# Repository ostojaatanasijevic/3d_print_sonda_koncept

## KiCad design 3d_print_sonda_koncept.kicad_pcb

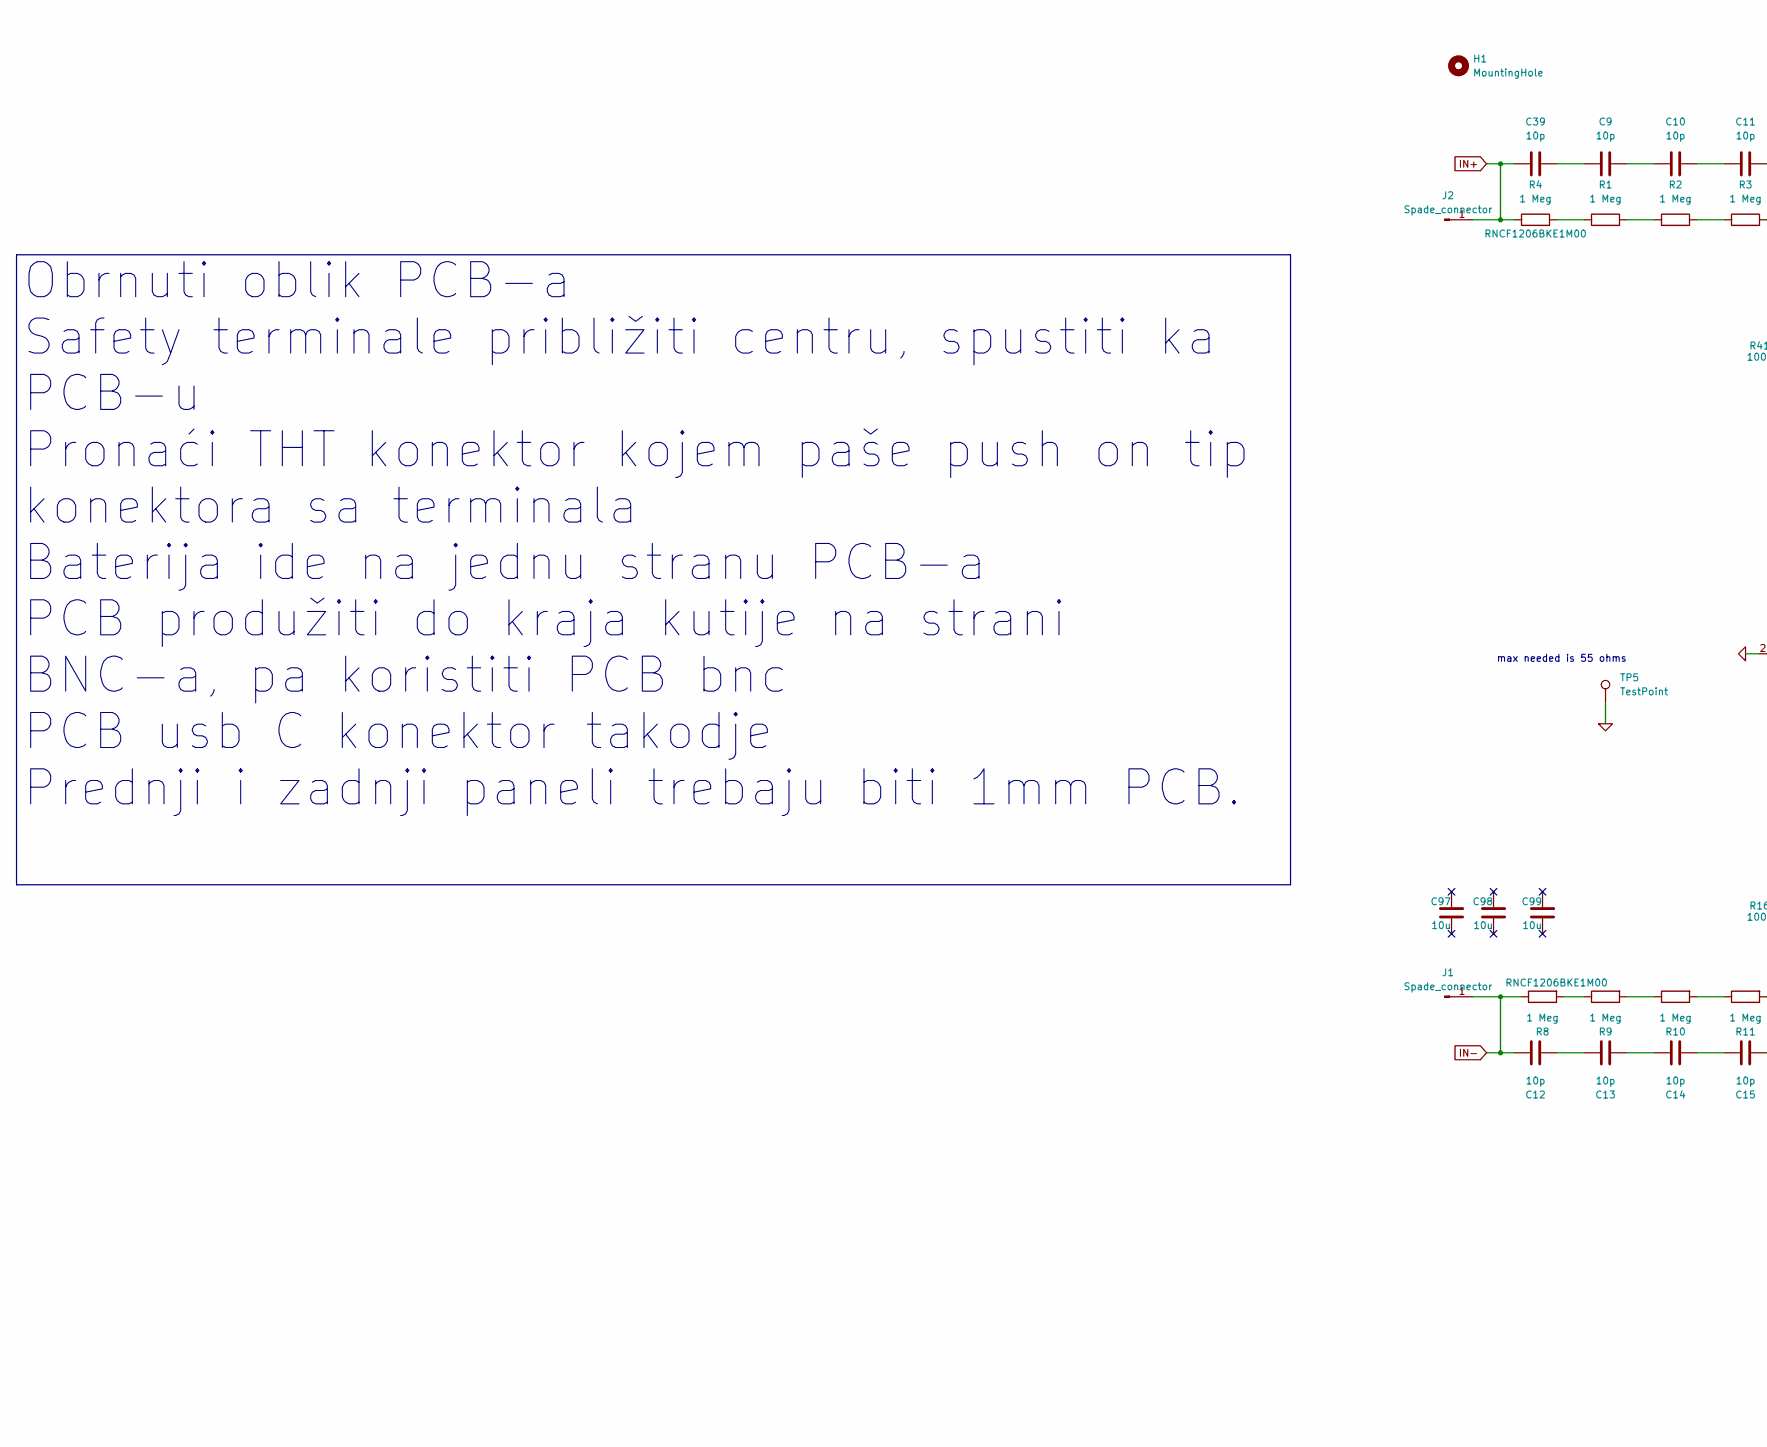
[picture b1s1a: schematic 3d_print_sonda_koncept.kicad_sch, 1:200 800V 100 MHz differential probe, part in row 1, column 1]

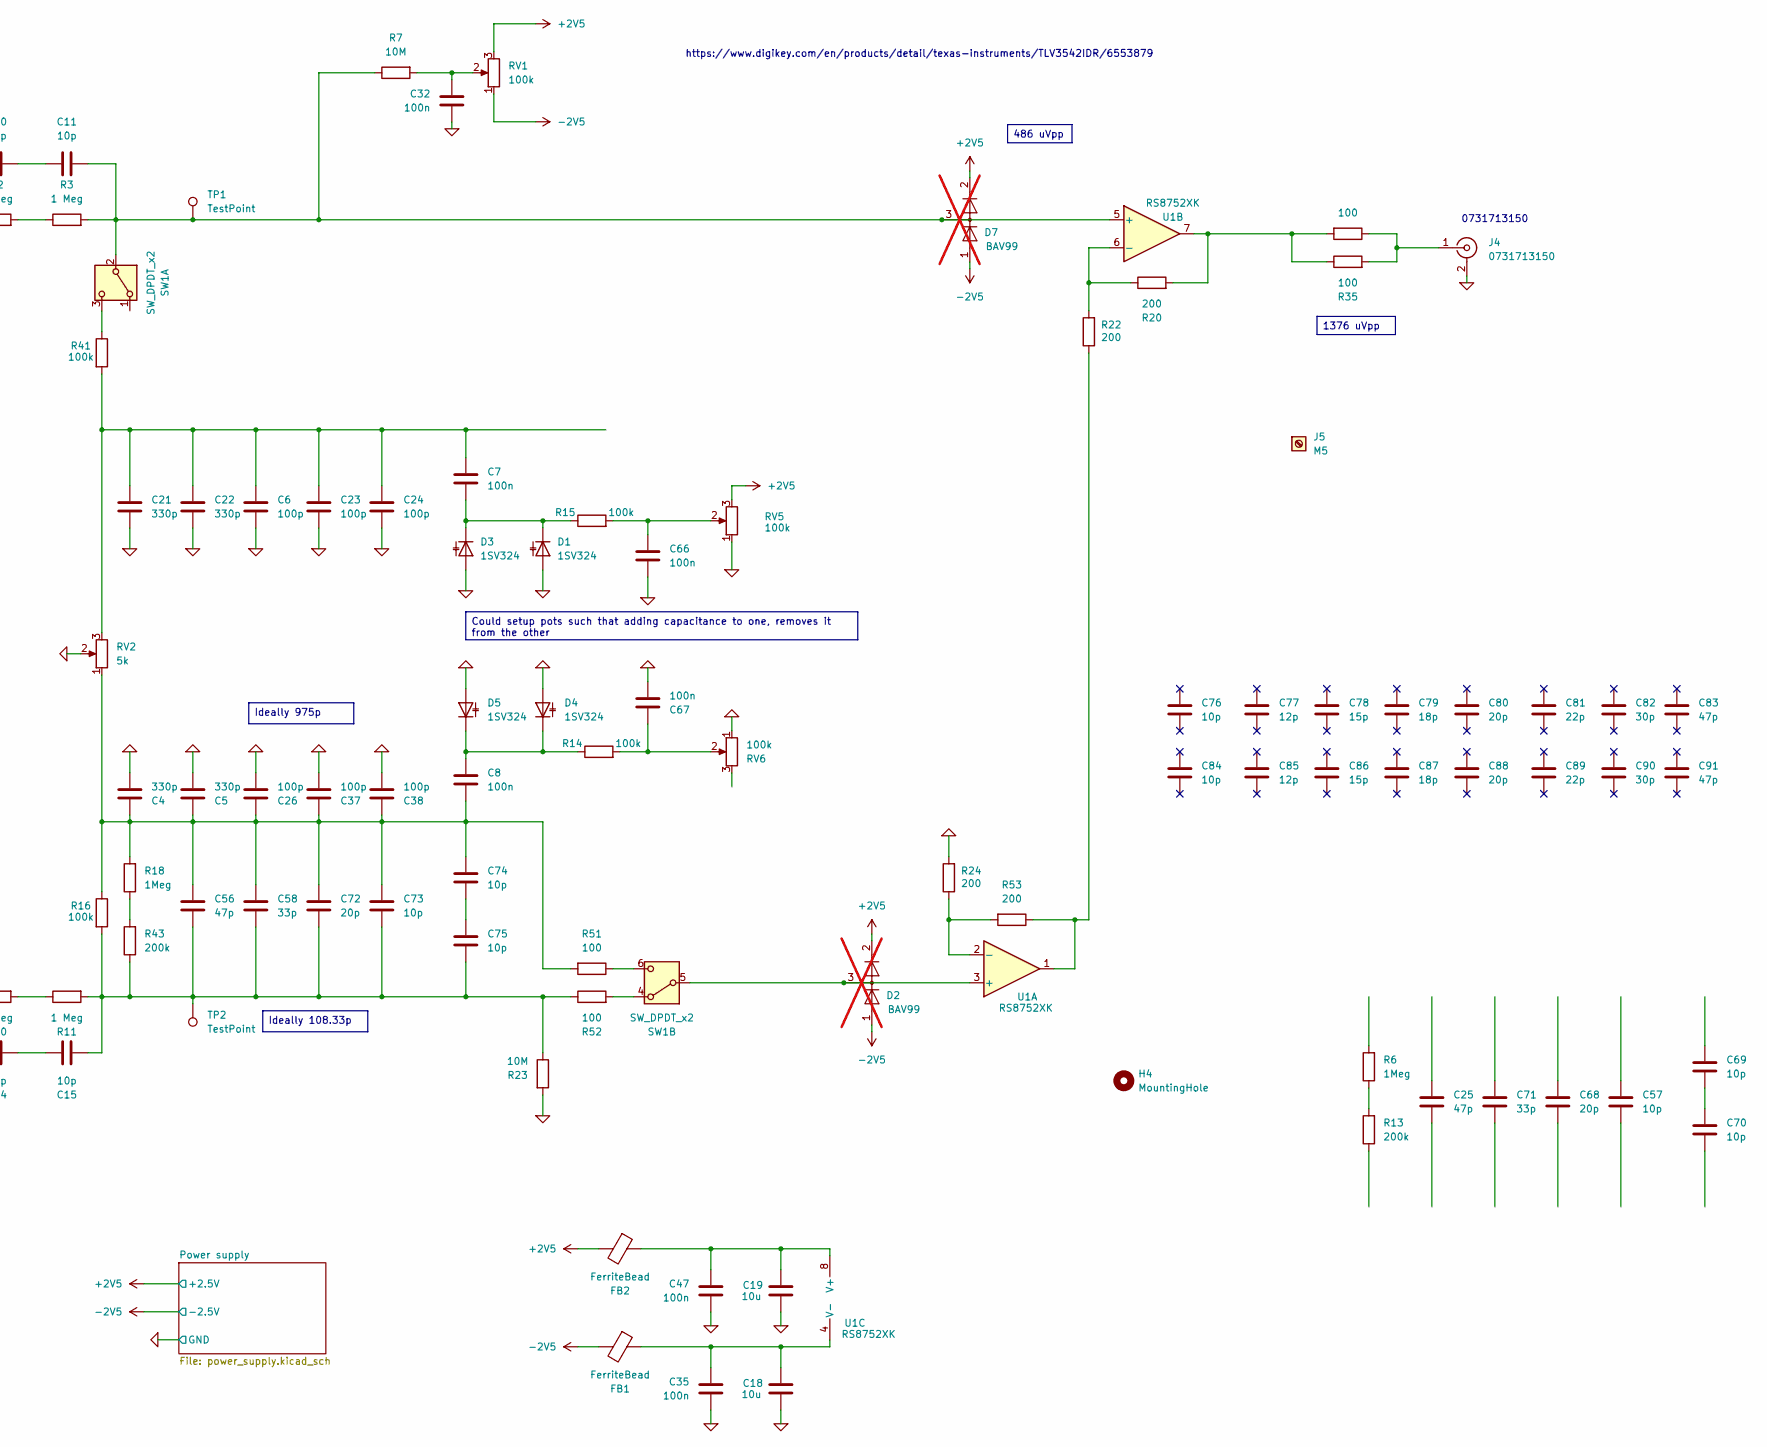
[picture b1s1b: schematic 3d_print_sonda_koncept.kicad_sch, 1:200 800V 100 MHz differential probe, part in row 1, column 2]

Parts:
C4, C5, C21, C22: 330p; R_0603_1608Metric_Pad0.98x0.95mm_HandSolder; LCSC C1664
C6, C23, C24, C26, C37, C38: 100p; R_0603_1608Metric_Pad0.98x0.95mm_HandSolder; LCSC C14858
C7, C8, C32, C35, C47, C66, C67: 100n; C_0603_1608Metric_Pad1.08x0.95mm_HandSolder; LCSC C14663
C9, C10, C11, C12, C13, C14, C15, C39: 10p; R_1206_3216Metric_Pad1.30x1.75mm_HandSolder
C18, C19: 10u; C_0603_1608Metric_Pad1.08x0.95mm_HandSolder; LCSC C96446
C25, C56, C83, C91: 47p; R_0603_1608Metric_Pad0.98x0.95mm_HandSolder; LCSC C1648
C57, C69, C70, C73, C74, C75, C76, C84: 10p; R_0603_1608Metric_Pad0.98x0.95mm_HandSolder; LCSC C1634
C58, C71: 33p; R_0603_1608Metric_Pad0.98x0.95mm_HandSolder; LCSC C1663
C68, C72, C80, C88: 20p; R_0603_1608Metric_Pad0.98x0.95mm_HandSolder; LCSC C1648
C77, C85: 12p; R_0603_1608Metric_Pad0.98x0.95mm_HandSolder; LCSC C38523
C78, C86: 15p; R_0603_1608Metric_Pad0.98x0.95mm_HandSolder; LCSC C1644
C79, C87: 18p; R_0603_1608Metric_Pad0.98x0.95mm_HandSolder; LCSC C1644
C81, C89: 22p; R_0603_1608Metric_Pad0.98x0.95mm_HandSolder; LCSC C1653
C82, C90: 30p; R_0603_1608Metric_Pad0.98x0.95mm_HandSolder; LCSC C1658
C97, C98, C99: 10u; R_0805_2012Metric_Pad1.20x1.40mm_HandSolder; Voltage 25V; LCSC C15850
D1, D3, D4, D5: 1SV324; D_SOD-323_HandSoldering
D2, D7: BAV99; SOT-23; LCSC C2500; not fitted
FB1, FB2: FerriteBead; L_0603_1608Metric_Pad1.05x0.95mm_HandSolder
H1, H4: MountingHole; M3_with_screw
J1, J2: Spade_connector; spade_connector_mid_PCB
J4: 0731713150; 5414373-1
J5: M5; M5_floating
R1, R2, R3, R9, R10, R11: 1 Meg; R_1206_3216Metric_Pad1.30x1.75mm_HandSolder
R4, R8: 1 Meg; R_1206_3216Metric_Pad1.30x1.75mm_HandSolder; Partnumber RNCF1206BKE1M00
R6, R18: 1Meg; R_0603_1608Metric_Pad0.98x0.95mm_HandSolder; LCSC C22935
R7, R23: 10M; R_0603_1608Metric_Pad0.98x0.95mm_HandSolder; LCSC C7250
R13, R43: 200k; R_0603_1608Metric_Pad0.98x0.95mm_HandSolder; LCSC C25811
R14, R15, R16, R41: 100k; R_0603_1608Metric_Pad0.98x0.95mm_HandSolder; LCSC C25803
R17, R35, R51, R52: 100; R_0603_1608Metric_Pad0.98x0.95mm_HandSolder; LCSC C22775
R20, R22, R24, R53: 200; R_0603_1608Metric_Pad0.98x0.95mm_HandSolder
RV1, RV5, RV6: 100k; Potentiometer_Bourns_3296W_Vertical
RV2: 5k; Potentiometer_Bourns_3296W_Vertical
SW1: SW_DPDT_x2; DPDT_bigger
TP1, TP2, TP5: TestPoint; TestPoint_Pad_D2.0mm
U1: RS8752XK; SOIC-8_3.9x4.9mm_P1.27mm; LCSC RS8752XK

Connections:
0: C4.2, C5.2, C6.1, C18.2, C19.2, C21.2, C22.2, C23.1, C24.1, C26.1, C32.1, C35.1, C37.1, C38.1, C47.1, C66.1, C67.1, D1.2 (A), D3.2 (A), D4.2 (A), D5.2 (A), J4.2 (Ext), R23.2, R24.2, RV2.2, RV5.1, RV6.1, TP5.1; also elsewhere on the board
+2V5: D2.2 (A), D7.2 (A), FB2.2, RV1.3, RV5.3; also elsewhere on the board
-2V5: D2.1 (K), D7.1 (K), FB1.2, RV1.1; also elsewhere on the board
IN+: C39.2, J2.1, R4.1
IN-: C12.2, J1.1, R8.1
unnamed: C10.1, C11.2
unnamed: C9.1, C10.2
unnamed: C12.1, C13.2
unnamed: C13.1, C14.2
unnamed: C14.1, C15.2
unnamed: C15.1, C56.1, C58.1, C72.1, C73.1, C75.1, R11.2, R16.2, R23.1, R43.1, R52.1, TP2.1
unnamed: C6.2, C7.2, C21.1, C22.1, C23.2, C24.2, R41.2, RV2.3
unnamed: C4.1, C5.1, C8.1, C26.2, C37.2, C38.2, C56.2, C58.2, C72.2, C73.2, C74.2, R16.1, R18.2, R51.2, RV2.1
unnamed: C32.2, R7.2, RV1.2
unnamed: C9.2, C39.1
unnamed: C66.2, R15.2, RV5.2
unnamed: C67.2, R14.2, RV6.2
unnamed: C69.1, C70.2
unnamed: C74.1, C75.2
unnamed: C7.1, D1.1 (K), D3.1 (K), R15.1
unnamed: C8.2, D4.1 (K), D5.1 (K), R14.1
unnamed: J4.1 (In), R17.1, R35.2
unnamed: R1.1, R4.2
unnamed: R1.2, R2.1
unnamed: R2.2, R3.1
unnamed: R8.2, R9.1
unnamed: R9.2, R10.1
unnamed: R10.2, R11.1
unnamed: R6.1, R13.2
unnamed: R17.2, R20.2, R35.1, U1.7
unnamed: R18.1, R43.2
unnamed: R22.1, R53.1, U1.1
unnamed: C11.1, D7.3 (K), R3.2, R7.1, SW1.2 (B), TP1.1, U1.5 (+)
unnamed: R41.1, SW1.3 (C)
unnamed: R52.2, SW1.4 (A)
unnamed: D2.3 (K), SW1.5 (B), U1.3 (+)
unnamed: R51.1, SW1.6 (C)
unnamed: R24.1, R53.2, U1.2 (-)
unnamed: R20.1, R22.2, U1.6 (-)
unnamed: C19.1, C47.2, FB2.1, U1.8 (V+)
unnamed: C18.1, C35.2, FB1.1, U1.4 (V-)

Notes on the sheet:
https://www.digikey.com/en/products/detail/texas-instruments/TLV3542IDR/6553879
max needed is 55 ohms
0731713150
1376 uVpp
Ideally 108.33p
Ideally 975p
486 uVpp
Could setup pots such that adding capacitance to one, removes it from the other
Obrnuti oblik PCB-a Safety terminale približiti centru, spustiti ka PCB-u Pronaći THT konektor kojem paše push on tip konektora sa terminala Baterija ide na jednu stranu PCB-a PCB produžiti do kraja kutije na strani BNC-a, pa koristiti PCB bnc PCB usb C konektor takodje Prednji i zadnji paneli treb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

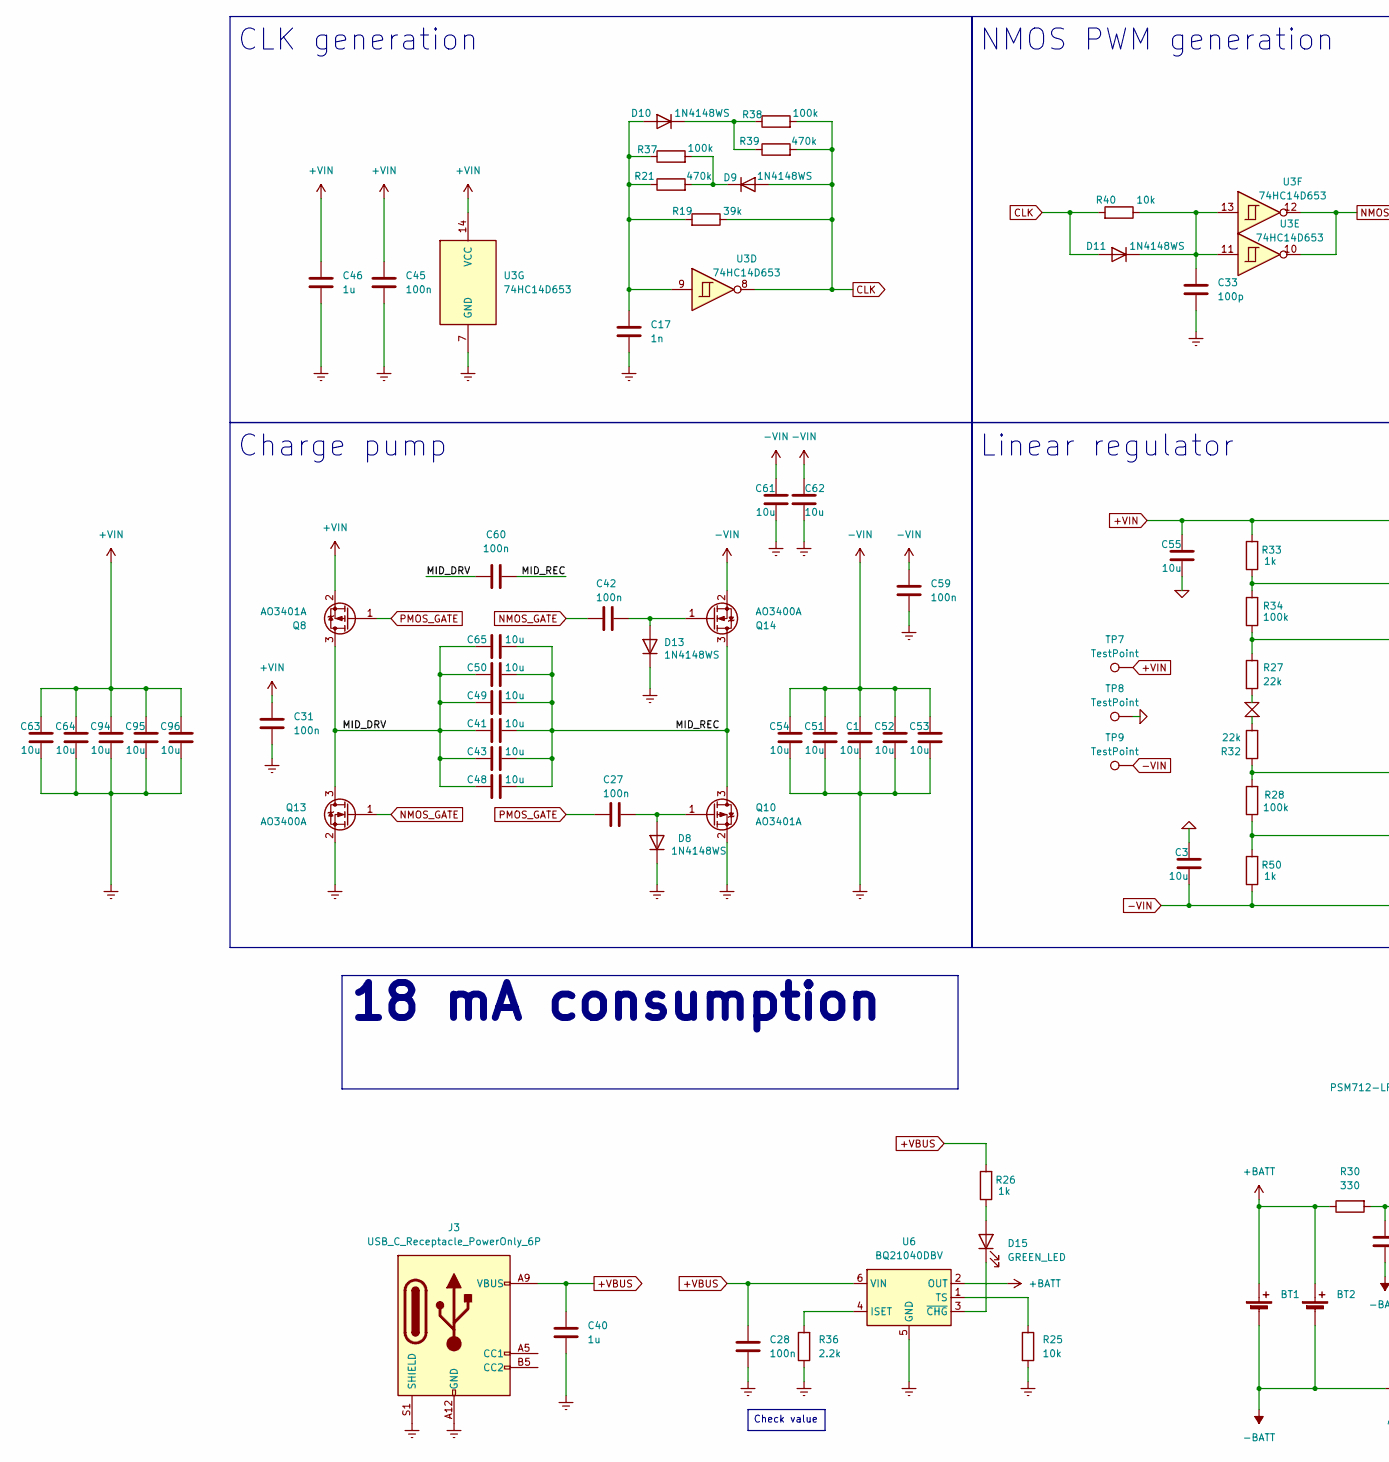
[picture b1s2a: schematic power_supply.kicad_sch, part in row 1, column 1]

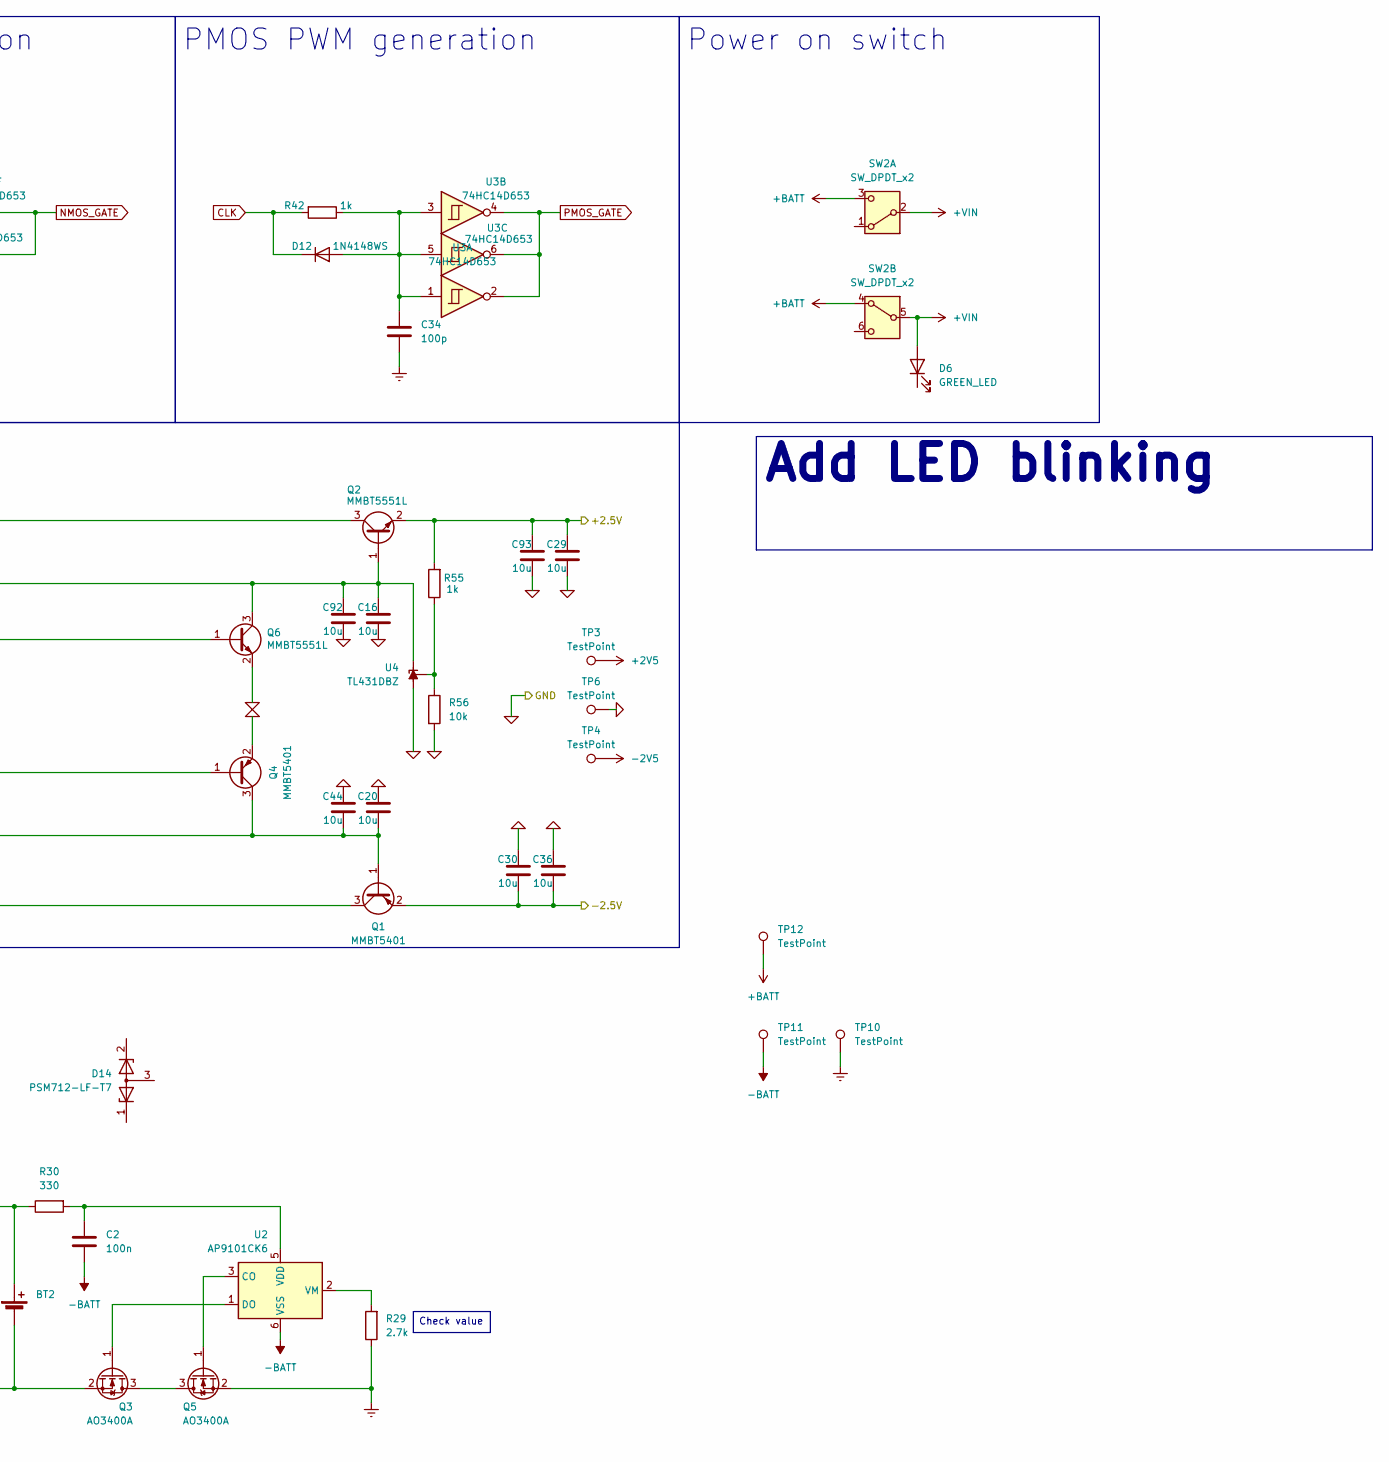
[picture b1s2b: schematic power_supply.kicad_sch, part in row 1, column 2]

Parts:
BT1, BT2: Battery_Cell; battery_holder
C1, C3, C16, C20, C29, C30, C36, C41, C43, C44, C48, C49, C50, C51, C52, C53, C54, C55, C61, C62, C63, C64, C65, C92, C93, C94, C95, C96: 10u; R_0805_2012Metric_Pad1.20x1.40mm_HandSolder; Voltage 25V; LCSC C15850
C2, C27, C28, C31, C42, C45, C59, C60: 100n; C_0603_1608Metric_Pad1.08x0.95mm_HandSolder; LCSC C14663
C17: 1n; C_0603_1608Metric_Pad1.08x0.95mm_HandSolder; LCSC C1588
C33, C34: 100p; C_0603_1608Metric_Pad1.08x0.95mm_HandSolder; LCSC C14858
C40, C46: 1u; C_0603_1608Metric_Pad1.08x0.95mm_HandSolder; LCSC C15849
D6, D15: GREEN_LED; LED_0805_2012Metric_Pad1.15x1.40mm_HandSolder; LCSC C2297
D8, D9, D10, D11, D12, D13: 1N4148WS; D_SOD-323; LCSC C2128
D14: PSM712-LF-T7; SOT-23_Handsoldering; LCSC C32677
J3: USB_C_Receptacle_PowerOnly_6P; USB_C_Receptacle_GCT_USB4125-xx-x-0190_6P_TopMnt_Horizontal
Q1, Q4: MMBT5401; SOT-23; LCSC C8326
Q2, Q6: MMBT5551L; SOT-23; LCSC C2145
Q3, Q5, Q13, Q14: AO3400A; SOT-23; LCSC C20917
Q8, Q10: AO3401A; SOT-23; LCSC C15127
R19: 39k; R_0603_1608Metric_Pad0.98x0.95mm_HandSolder; LCSC C23153
R21, R39: 470k; R_0603_1608Metric_Pad0.98x0.95mm_HandSolder; LCSC C23178
R25, R40, R56: 10k; R_0603_1608Metric_Pad0.98x0.95mm_HandSolder; LCSC C25804
R26, R33, R42, R50, R55: 1k; R_0603_1608Metric_Pad0.98x0.95mm_HandSolder; LCSC C21190
R27, R32: 22k; R_0603_1608Metric_Pad0.98x0.95mm_HandSolder; LCSC C31850
R28, R34, R37, R38: 100k; R_0603_1608Metric_Pad0.98x0.95mm_HandSolder; LCSC C25803
R29: 2.7k; R_0603_1608Metric_Pad0.98x0.95mm_HandSolder; LCSC C13167
R30: 330; R_0603_1608Metric_Pad0.98x0.95mm_HandSolder; LCSC C23138
R36: 2.2k; R_0603_1608Metric_Pad0.98x0.95mm_HandSolder; LCSC C4190
SW2: SW_DPDT_x2; DPDT_bigger
TP3, TP4, TP6, TP7, TP8, TP9, TP10, TP11, TP12: TestPoint; TestPoint_Pad_D2.0mm
U2: AP9101CK6; SOT-23-6
U3: 74HC14D653; SOIC-14_3.9x8.7mm_P1.27mm; LCSC C5605
U4: TL431DBZ; SOT-23; LCSC C3113
U6: BQ21040DBV; SOT-23-6

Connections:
0: C3.2, C16.1, C20.2, C29.1, C30.2, C36.2, C44.2, C55.1, C92.1, C93.1, Q4.2 (E), Q6.2 (E), R27.2, R32.2, R56.2, TP6.1, TP8.1, U4.3 (A); also elsewhere on the board
+2V5: C29.2, C93.2, Q2.2 (E), R55.2, TP3.1; also elsewhere on the board
+BATT: BT1.1 (+), BT2.1 (+), R30.1, SW2.3 (C), SW2.4 (A), TP12.1, U6.2 (OUT)
+VBUS: C28.2, C40.2, J3.A9 (VBUS), J3.B9 (VBUS), R26.2, U6.6 (VIN)
+VIN: C31.2, C45.2, C46.2, C55.2, C63.2, C64.2, C94.2, C95.2, C96.2, D6.2 (A), Q2.3 (C), Q8.2 (S), R33.2, SW2.2 (B), SW2.5 (B), TP7.1, U3.14 (VCC)
-2V5: C30.1, C36.1, Q1.2 (E), TP4.1; also elsewhere on the board
-BATT: BT1.2 (-), BT2.2 (-), C2.1, Q3.2 (S), TP11.1, U2.6 (VSS)
-VIN: C1.2, C3.1, C51.2, C52.2, C53.2, C54.2, C59.2, C61.2, C62.2, Q1.3 (C), Q14.2 (S), R50.1, TP9.1
/Power supply/MID_DRV: C41.1, C43.1, C48.1, C49.1, C50.1, C60.2, C65.1, Q8.3 (D), Q13.3 (D)
/Power supply/MID_REC: C41.2, C43.2, C48.2, C49.2, C50.2, C60.1, C65.2, Q10.3 (D), Q14.3 (D)
CLK: D9.2 (A), D11.2 (A), D12.1 (K), R19.1, R38.2, R39.2, R40.2, R42.2, U3.8
Earth: C1.1, C17.1, C28.1, C31.1, C33.1, C34.1, C40.1, C45.1, C46.1, C51.1, C52.1, C53.1, C54.1, C59.1, C61.1, C62.1, C63.1, C64.1, C94.1, C95.1, C96.1, D8.1 (K), D13.1 (K), J3.A12 (GND), J3.B12 (GND), J3.S1 (SHIELD), Q5.2 (S), Q10.2 (S), Q13.2 (S), R25.2, R29.1, R36.1, TP10.1, U3.7 (GND), U6.5 (GND)
NMOS_GATE: C42.1, Q13.1 (G), U3.10, U3.12
unnamed: C27.2, D8.2 (A), Q10.1 (G)
unnamed: D9.1 (K), R21.2, R37.2
unnamed: C17.2, D10.2 (A), R19.2, R21.1, R37.1, U3.9
unnamed: D10.1 (K), R38.1, R39.1
unnamed: C33.2, D11.1 (K), R40.1, U3.11, U3.13
unnamed: C34.2, D12.2 (A), R42.1, U3.1, U3.3, U3.5
unnamed: C42.2, D13.2 (A), Q14.1 (G)
unnamed: D15.2 (A), R26.1
unnamed: D15.1 (K), U6.3 (~CHG)
unnamed: C20.1, C44.1, Q1.1 (B), Q4.3 (C), R28.1, R50.2
unnamed: C16.2, C92.2, Q2.1 (B), Q6.3 (C), R33.1, R34.2, U4.1 (K)
unnamed: Q3.3 (D), Q5.3 (D)
unnamed: Q3.1 (G), U2.1 (DO)
unnamed: Q4.1 (B), R28.2, R32.1
unnamed: Q5.1 (G), U2.3 (CO)
unnamed: Q6.1 (B), R27.1, R34.1
unnamed: C2.2, R30.2, U2.5 (VDD)
unnamed: R29.2, U2.2 (VM)
unnamed: R55.1, R56.1, U4.2 (REF)
unnamed: R36.2, U6.4 (ISET)
unnamed: R25.1, U6.1 (TS)
PMOS_GATE: C27.1, Q8.1 (G), U3.2, U3.4, U3.6

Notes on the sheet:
Charge pump
CLK generation
Power on switch
Linear regulator
PMOS PWM generation
NMOS PWM generation
18 mA consumption
Check value
Add LED blinking

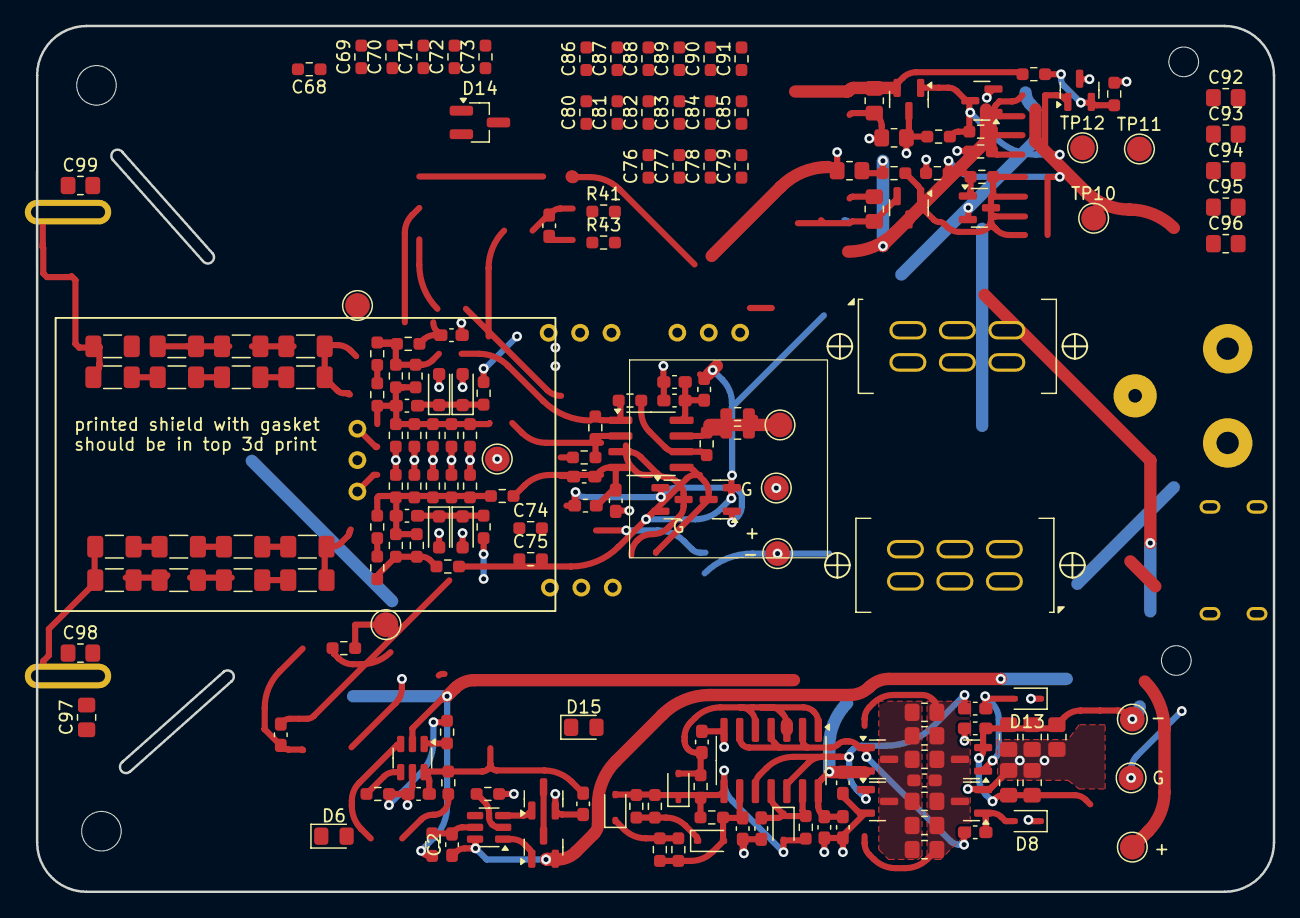
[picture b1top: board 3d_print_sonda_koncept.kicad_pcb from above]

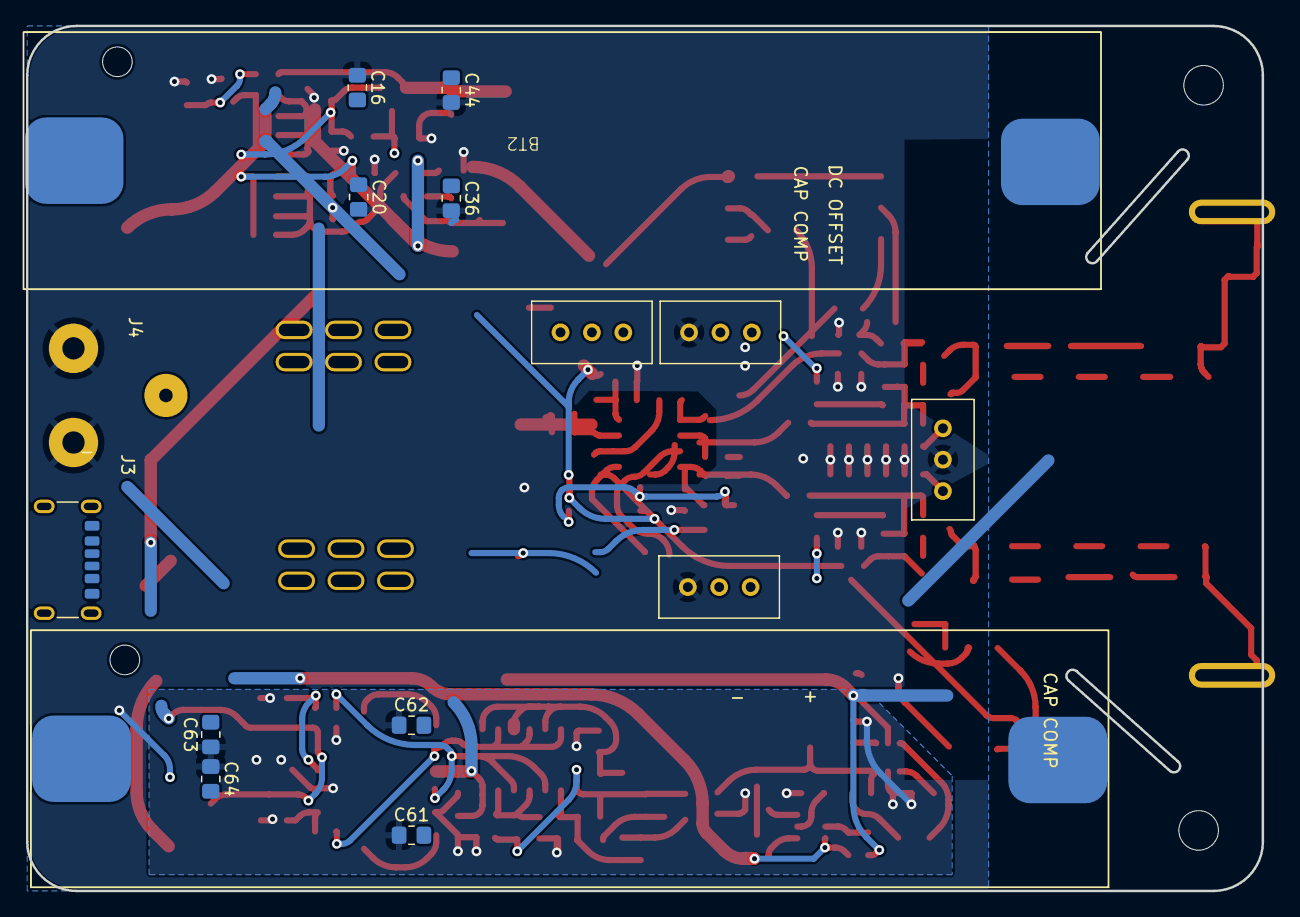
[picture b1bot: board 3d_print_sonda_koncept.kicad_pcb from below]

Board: 2 copper layers, 100.0 x 70.0 mm, 204 parts (20 on the bottom side), 73 nets.

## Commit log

2025-12-14 Some errors fixed.
2026-05-31 right angle 4 mm
2026-06-28 merge
2026-06-28 measuremment
